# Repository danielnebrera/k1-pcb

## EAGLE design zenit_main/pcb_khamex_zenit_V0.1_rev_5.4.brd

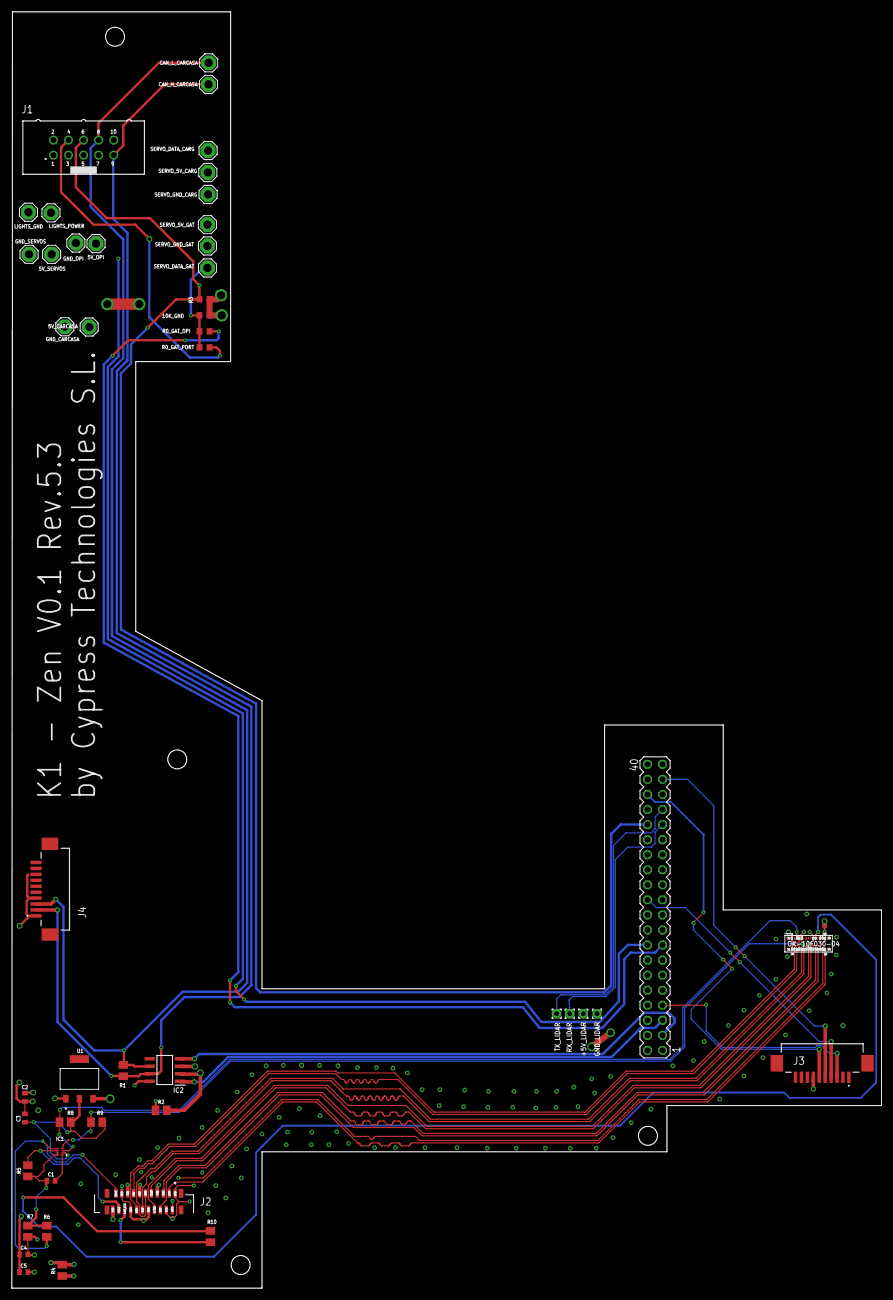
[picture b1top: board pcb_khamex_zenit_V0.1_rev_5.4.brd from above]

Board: 4 copper layers, 146.7 x 215.3 mm, 47 parts (0 on the bottom side), 44 nets.

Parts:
5V_CARCASA, 5V_OPI, 5V_SERVOS: SE14
10K_GND: 10k; R0603
+5V_LIDAR: WIREPAD1,6/0,8; 1,6/0,8
C1: 100pf_0603; CAPC1608X90N
C2, C3: 1uf_0603; CAPC1608X90N
C4: 100nf_0603; CAPC1608X90N
C5: 10uf_0603; CAPC1608X90N
CAN_H_CARCASA: SE14
CAN_L_CARCASA: SE14
GND_CARCASA: SE14
GND_LIDAR: WIREPAD1,6/0,8; 1,6/0,8
GND_OPI: SE14
GND_SERVOS: SE14
IC1: PCA9306JKZ
IC2: SN65HVD230DR; SOT127P600X175-8N
J1: 612010235121
J2: 52559-2253; 525592253
J3, J4: 686110188622
LIGHTS_GND: SE14
LIGHTS_POWER: SE14
R0_GAT_OPI, R0_GAT_PORT: 0Ω; R0603
R1: 120Ω; M0805
R2: 10k; M0805
R3: 10k; R0603
R4: 10k_0805; M0805
R5, R6, R8, R9: 2.2k_0805; M0805
R7: 200k_0805; M0805
R10: 0_oms; M0805
RX_LIDAR: WIREPAD1,6/0,8; 1,6/0,8
SERVO_5V_CARG, SERVO_5V_GAT: SE14
SERVO_DATA_CARG: SE14
SERVO_DATA_GAT: SE14
SERVO_GND_CARG: SE14
SERVO_GND_GAT: SE14
SV1: conector orange pi 5 ultra; MA20-2
TX_LIDAR: WIREPAD1,6/0,8; 1,6/0,8
U1: AMS1117-1.8; SOT229P700X180-4N
U$1: OK-10F030-04_DEVICE; OK-10F030-04_PACKAGE

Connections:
1.8V: C3.2, IC1.2, R8.2, R9.2, U1.2
3V3: C2.2, C4.2, C5.2, J2.22, R4.1, R7.2, U1.3, U$1.13, U$1.14
5V_CARCASA: 5V_CARCASA.MP, J4.1, J4.5, J4.6, J4.7
5V_OPI: 5V_OPI.MP, +5V_LIDAR.1, SV1.2, SV1.4
5V_SERVOS: 5V_SERVOS.MP, SERVO_5V_CARG.MP, SERVO_5V_GAT.MP
CAM_CLK: J2.18, R10.2
CANH: CAN_H_CARCASA.MP, IC2.7, J1.9, J4.2, R1.1
CANL: CAN_L_CARCASA.MP, IC2.6, J1.8, J4.3, R1.2
CLK: R10.1, U$1.11
CLKN: J2.8, U$1.23
CLKP: J2.9, U$1.22
D0N: J2.2, U$1.17
D0P: J2.3, U$1.16
D1N: J2.5, U$1.20
D1P: J2.6, U$1.19
D2N: J2.11, U$1.26
D2P: J2.12, U$1.25
D3N: J2.14, U$1.29
D3P: J2.15, U$1.28
GND_CARCASA: GND_CARCASA.MP, J4.4, J4.8, J4.9, J4.10
GND_OPI: 10K_GND.2, C2.1, C3.1, C4.1, C5.1, GND_LIDAR.1, GND_OPI.MP, IC2.2, J1.5, J1.7, J1.10, J2.1, J2.4, J2.7, J2.10, J2.13, J2.16, J2.19, R2.1, R3.1, SV1.6, SV1.9, SV1.14, SV1.20, SV1.25, SV1.34, SV1.39, U1.1, U$1.1, U$1.4, U$1.10, U$1.15, U$1.18, U$1.21, U$1.24, U$1.27, U$1.30
GND_SERVOS: GND_SERVOS.MP, SERVO_GND_CARG.MP, SERVO_GND_GAT.MP
GPIO-BTN1: J3.3, SV1.7
GPIO-BTN2: J3.4, SV1.22
GPIO-LED1: J3.5, SV1.37
GPIO-LED2: J3.6, SV1.36
unnamed: C1.1, IC1.1
unnamed: C1.2, IC1.7, IC1.8, R5.2, R6.2, R7.1
unnamed: J2.17, R4.2
unnamed: IC2.8, R2.2
OPI_CAN_RX: IC2.4, SV1.3
OPI_CAN_TX: IC2.1, SV1.5
PWM_GATILLO_OPI: R0_GAT_OPI.1, SV1.15
PWM_GATILLO_PORT: J1.4, R0_GAT_PORT.2
PWM_SYNC: J1.6, R3.2, SV1.32
RX_LIDAR: RX_LIDAR.1, SV1.31
SCL1: IC1.3, R8.1, U$1.3
SCL2: IC1.6, J2.20, R5.1
SDA1: IC1.4, R9.1, U$1.5
SDA2: IC1.5, J2.21, R6.1
SERVO_CARGADOR_DATA: SERVO_DATA_CARG.MP, SV1.16
SERVO_GATILLO_DATA: 10K_GND.1, R0_GAT_OPI.2, R0_GAT_PORT.1, SERVO_DATA_GAT.MP
TX_LIDAR: SV1.33, TX_LIDAR.1
VCC_3.3V: IC2.3, J3.7, SV1.1

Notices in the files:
parts and their libraries:
Eagle_WR-BHD_rev24a: Copyright: Würth Elektronik
